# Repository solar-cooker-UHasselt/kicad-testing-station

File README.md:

# kicad-testing-station

The main board of the [solar cooker](https://github.com/solar-cooker-UHasselt) testing
station: a shield for the
[Arduino UNO R4 WiFi](https://docs.arduino.cc/hardware/uno-r4-wifi/) that logs how a
solar cooker performs. With the firmware
([arduino-code](https://github.com/solar-cooker-UHasselt/arduino-code)) it records:

- the temperature in three pots, with PT100 probes on three MAX31865 circuits
- the solar irradiance, with a pyranometer
- the wind speed, with an anemometer
- the outside temperature, with an AM2315C sensor
- the air pressure and humidity inside the box, with a BME680

Every measurement goes to a CSV file on a microSD card, stamped by a DS3231 real-time
clock, and shows on an LCD. The MAX31865, BME680, DS3231 and microSD circuits are
Adafruit's breakouts, drawn onto the shield as schematic sheets. Each also has its own
repo, see the [board overview](https://solar-cooker-uhasselt.github.io/). The sensors outside the box
connect to screw terminals, the LCD to a 20-pin FPC connector.

- [Board page](https://solar-cooker-uhasselt.github.io/kicad-testing-station/): 3D
  renders, drawings, schematic and board PDF, interactive BOM and the BOM CSV for
  Eurocircuits, rebuilt by CI on every push to `main`
- [Port an Eagle design to KiCad](docs/eagle_to_kicad.md): how the Adafruit and
  Arduino parts were brought into KiCad, and replacing symbols and footprints
- [PCB manufacturing](docs/pcb_manufacturing.md): the Eurocircuits BOM and checking
  part availability
- [KiCad tools](docs/kicad_tools.md): Freerouting, KiBot, KiKit and Kiri

## Installation

### Requirements

- [KiCad 10](https://www.kicad.org/download/), to open and edit the board
- [git](https://git-scm.com), to clone the repo
- Optional, for the checks: [just](https://just.systems)

### Clone

```bash
git clone https://github.com/solar-cooker-UHasselt/kicad-testing-station.git
```

Own symbols, footprints and 3D models are in `external/`, in the repo itself.

## Usage

Open `testing-station.kicad_pro` in KiCad 10. The schematic, with a sheet per breakout
circuit, and the board open from there.

Before committing, run ERC and DRC, reports in `tmp/`:

```bash
just check
```

`just --list` shows the other recipes: PDFs, and the CI workflow run locally.

## Contributing

- Work on a branch and open a pull request to `main`. It merges once CI passes and a code
  owner (listed in [.github/CODEOWNERS](.github/CODEOWNERS)) approves it. `main`
  accepts no force pushes.
- CI runs ERC and DRC on every pull request, through the shared workflows in
  [kicad-ci](https://github.com/solar-cooker-UHasselt/kicad-ci). `just check` runs the
  same check locally. A push to `main` that changes more than Markdown also rebuilds
  the board page.
- Commits follow Conventional Commits, with one change per commit. Types, scopes and the
  ERC/DRC check are in
  [.agents/commit_conventions.md](.agents/commit_conventions.md).
- Changes to the board setup, CI or docs are made and tested in
  [kicad-adafruit-ds3231](https://github.com/solar-cooker-UHasselt/kicad-adafruit-ds3231)
  first, then copied here.

## Authors and acknowledgment

The breakout circuits are Adafruit's designs, by Limor Fried/Ladyada for Adafruit
Industries
([source files](https://learn.adafruit.com/accessing-and-using-adafruit-pcb-design-files/finding-and-downloading)).
The shield follows Arduino's
[UNO R4 WiFi design files](https://docs.arduino.cc/hardware/uno-r4-wifi/). The board
is by Lowie Van Vyve for the UHasselt solar cooker project.

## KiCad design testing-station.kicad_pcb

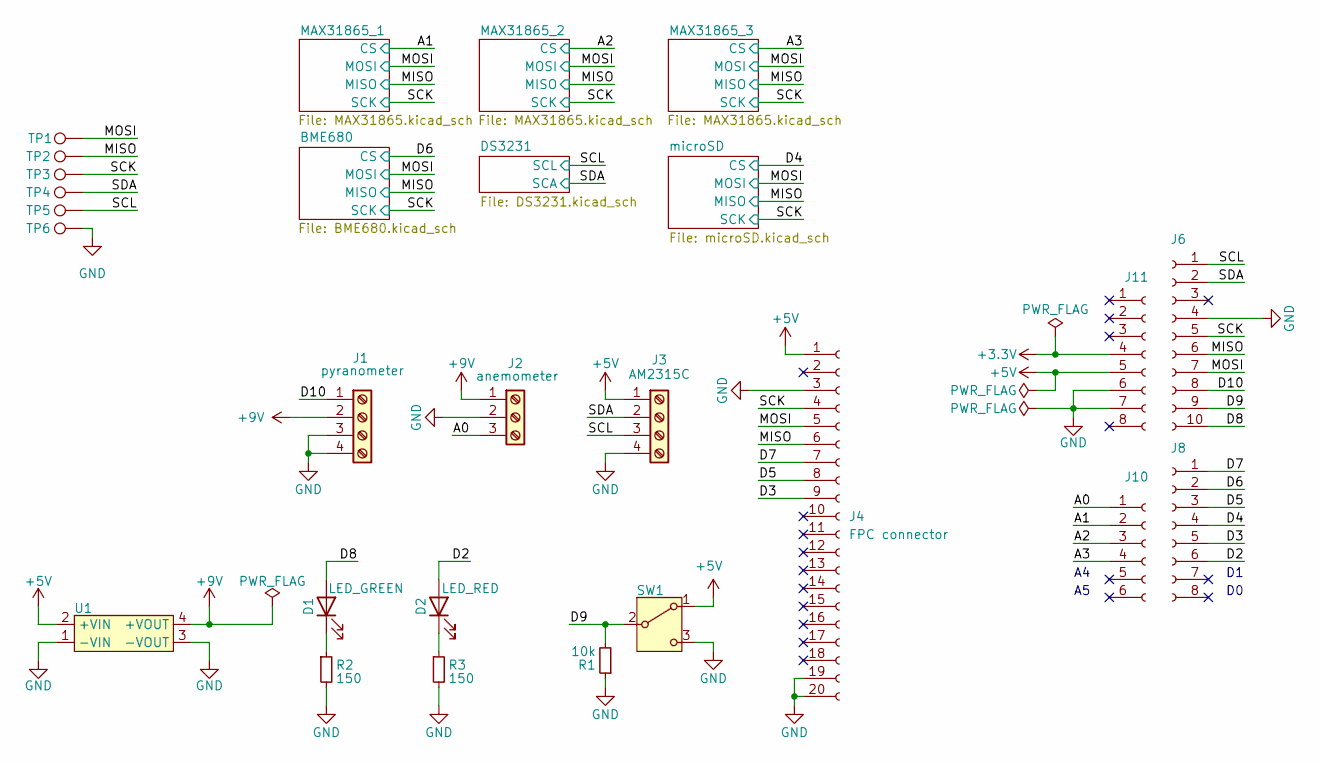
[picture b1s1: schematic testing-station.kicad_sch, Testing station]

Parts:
D1: LED_GREEN; LED_1206_3216Metric_Pad1.42x1.75mm_HandSolder; MPN 150120VS75000
D2: LED_RED; LED_1206_3216Metric_Pad1.42x1.75mm_HandSolder; MPN QTLP650D2TR
J1: pyranometer; TerminalBlock_4Ucon_1x04_P3.50mm_Horizontal; MPN 039357-0004
J2: anemometer; TerminalBlock_4Ucon_1x03_P3.50mm_Horizontal; MPN 039357-0003
J3: AM2315C; TerminalBlock_4Ucon_1x04_P3.50mm_Horizontal; MPN 039357-0004
J4: FPC connector; XF2M-1815-1A; MPN XF2M-1815-1A
J6: Conn_01x10_Socket; PinSocket_1x10_P2.54mm_Vertical; MPN SSQ-110-01-G-S
J8, J11: Conn_01x08_Socket; PinSocket_1x08_P2.54mm_Vertical; MPN SSQ-108-01-G-S
J10: Conn_01x06_Socket; PinSocket_1x06_P2.54mm_Vertical; MPN SSQ-106-01-G-S
R1: 10k; R_1206_3216Metric_Pad1.30x1.75mm_HandSolder; MPN /
R2, R3: 150; R_1206_3216Metric_Pad1.30x1.75mm_HandSolder; MPN /
SW1: 500SSP1S2M2QEA; MPN 500SSP1S2M2QEA
TP1: MOSI; TestPoint_Pad_D1.0mm
TP2: MISO; TestPoint_Pad_D1.0mm
TP3: SCK; TestPoint_Pad_D1.0mm
TP4: SDA; TestPoint_Pad_D1.0mm
TP5: SCL; TestPoint_Pad_D1.0mm
TP6: GND; TestPoint_Pad_D1.0mm
U1: TBA_1-0519; MPN TBA 1-0519

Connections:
+3.3V: J11.4; also elsewhere on the board
+5V: J3.1, J4.1, J11.5, SW1.1 (A), U1.2 (+VIN); also elsewhere on the board
+9V: J1.2, J2.1, U1.4 (+VOUT)
/A0: J2.3, J10.1
/A1: J10.2; also elsewhere on the board
/A2: J10.3; also elsewhere on the board
/A3: J10.4; also elsewhere on the board
/D2: D2.2 (A), J8.6
/D3: J4.9, J8.5
/D4: J8.4; also elsewhere on the board
/D5: J4.8, J8.3
/D6: J8.2; also elsewhere on the board
/D7: J4.7, J8.1
/D8: D1.2 (A), J6.10
/D9: J6.9, R1.2, SW1.2 (B)
/D10: J1.1, J6.8
/MISO: J4.6, J6.6, TP2.1; also elsewhere on the board
/MOSI: J4.5, J6.7, TP1.1; also elsewhere on the board
/SCK: J4.4, J6.5, TP3.1; also elsewhere on the board
/SCL: J3.3, J6.1, TP5.1; also elsewhere on the board
/SDA: J3.2, J6.2, TP4.1; also elsewhere on the board
GND: J1.3, J1.4, J2.2, J3.4, J4.3, J4.19, J4.20, J6.4, J11.6, J11.7, R1.1, R2.2, R3.2, SW1.3 (C), TP6.1, U1.1 (-VIN), U1.3 (-VOUT); also elsewhere on the board
unnamed: D1.1 (K), R2.1
unnamed: D2.1 (K), R3.1

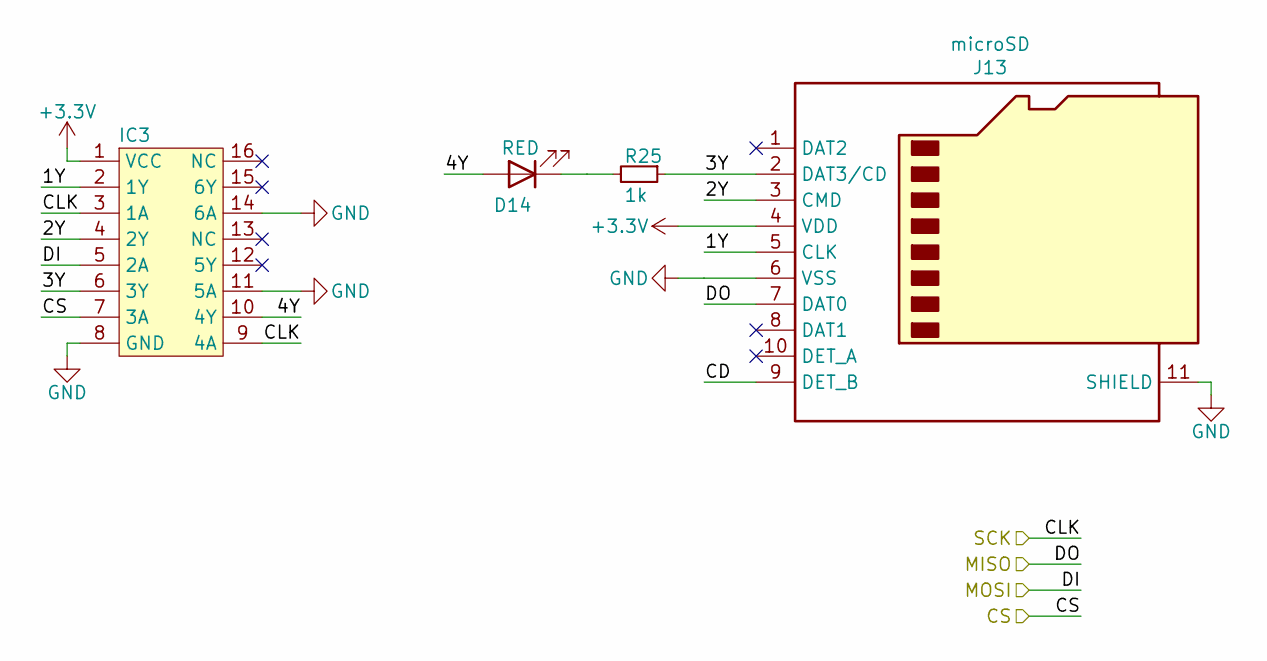
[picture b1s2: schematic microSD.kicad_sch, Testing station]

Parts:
D14: RED; LED_0805_2012Metric; MPN 150080SS75000
IC3: 74HC4050D; SOIC-16_3.9x9.9mm_P1.27mm; MPN 74HC4050D
J13: microSD; MEM2061-01-188-00-A; MPN MEM2061-01-188-00-A
R25: 1k; R_0805_2012Metric; MPN /

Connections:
+3.3V: IC3.1 (VCC), J13.4 (VDD); also elsewhere on the board
/D4: IC3.7 (3A); also elsewhere on the board
/MISO: J13.7 (DAT0); also elsewhere on the board
/MOSI: IC3.5 (2A); also elsewhere on the board
/SCK: IC3.3 (1A), IC3.9 (4A); also elsewhere on the board
/microSD/1Y: IC3.2 (1Y), J13.5 (CLK)
/microSD/2Y: IC3.4 (2Y), J13.3 (CMD)
/microSD/3Y: IC3.6 (3Y), J13.2 (DAT3/CD), R25.1
/microSD/4Y: D14.2 (A), IC3.10 (4Y)
/microSD/CD: J13.9 (DET_B)
GND: IC3.8 (GND), IC3.11 (5A), IC3.14 (6A), J13.6 (VSS), J13.11 (SHIELD); also elsewhere on the board
unnamed: D14.1 (K), R25.2

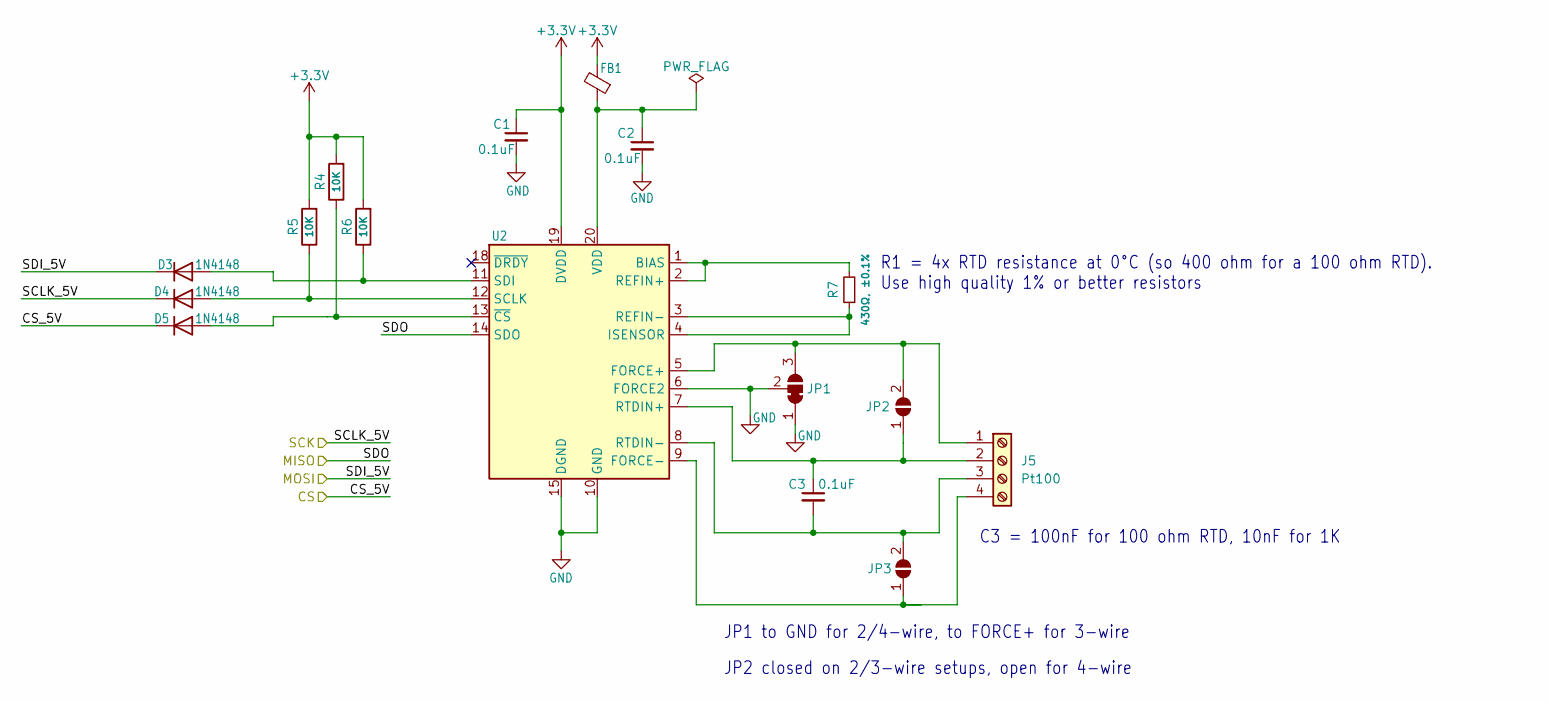
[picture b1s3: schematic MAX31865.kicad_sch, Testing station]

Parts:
C1, C2, C3: 0.1uF; C_0805_2012Metric; MPN /
D3, D4, D5: 1N4148; D_SOD-323; MPN 1N4148WX-TP
FB1: FERRITE-0805NO; LI0805G201R-10; MPN LI0805G201R-10
J5: Pt100; TerminalBlock_4Ucon_1x04_P3.50mm_Horizontal; MPN 039357-0004
JP1: SolderJumper_3_Bridged12; SolderJumper-3_P1.3mm_Bridged12_Pad1.0x1.5mm
JP2, JP3: SOLDERJUMPER; SolderJumper-2_P1.3mm_Open_RoundedPad1.0x1.5mm
R4, R5, R6: 10K; R_0805_2012Metric; MPN /
R7: 430Ω, ±0.1%; R_0805_2012Metric; MPN /
U2: MAX31865; MAX31865ATP+; MPN MAX31865ATP+

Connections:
+3.3V: C1.1, FB1.2, R4.2, R5.2, R6.2, U2.19 (DVDD); also elsewhere on the board
/A1: D5.1 (K); also elsewhere on the board
/MISO: U2.14 (SDO); also elsewhere on the board
/MOSI: D3.1 (K); also elsewhere on the board
/SCK: D4.1 (K); also elsewhere on the board
GND: C1.2, C2.2, JP1.1 (A), JP1.2 (C), U2.6 (FORCE2), U2.10 (GND), U2.15 (DGND), U2.16 (GND), U2.21 (GND); also elsewhere on the board
unnamed: D3.2 (A), R6.1, U2.11 (SDI)
unnamed: D4.2 (A), R5.1, U2.12 (SCLK)
unnamed: D5.2 (A), R4.1, U2.13 (~CS)
unnamed: J5.1, JP1.3 (B), JP2.2 (B), U2.5 (FORCE+)
unnamed: C3.1, J5.2, JP2.1 (A), U2.7 (RTDIN+)
unnamed: C3.2, J5.3, JP3.2 (B), U2.8 (RTDIN-)
unnamed: J5.4, JP3.1 (A), U2.9 (FORCE-)
unnamed: R7.2, U2.1 (BIAS), U2.2 (REFIN+)
unnamed: R7.1, U2.3 (REFIN-), U2.4 (ISENSOR)
unnamed: C2.1, FB1.1, U2.20 (VDD)

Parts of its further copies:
C6, C7, C8, C11, C12, C13: 0.1uF; C_0805_2012Metric; MPN /
D6, D7, D8, D9, D10, D11: 1N4148; D_SOD-323; MPN 1N4148WX-TP
FB2, FB3: FERRITE-0805NO; LI0805G201R-10; MPN LI0805G201R-10
J7, J9: Pt100; TerminalBlock_4Ucon_1x04_P3.50mm_Horizontal; MPN 039357-0004
JP4, JP7: SolderJumper_3_Bridged12; SolderJumper-3_P1.3mm_Bridged12_Pad1.0x1.5mm
JP5, JP6, JP8, JP9: SOLDERJUMPER; SolderJumper-2_P1.3mm_Open_RoundedPad1.0x1.5mm
R8, R9, R10, R12, R13, R14: 10K; R_0805_2012Metric; MPN /
R11, R15: 430Ω, ±0.1%; R_0805_2012Metric; MPN /
U4, U6: MAX31865; MAX31865ATP+; MPN MAX31865ATP+

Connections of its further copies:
+3.3V: C6.1, C11.1, FB2.2, FB3.2, R8.2, R9.2, R10.2, R12.2, R13.2, R14.2, U4.19 (DVDD), U6.19 (DVDD); also elsewhere on the board
/A2: D8.1 (K); also elsewhere on the board
/A3: D11.1 (K); also elsewhere on the board
/MISO: U4.14 (SDO), U6.14 (SDO); also elsewhere on the board
/MOSI: D6.1 (K), D9.1 (K); also elsewhere on the board
/SCK: D7.1 (K), D10.1 (K); also elsewhere on the board
GND: C6.2, C7.2, C11.2, C12.2, JP4.1 (A), JP4.2 (C), JP7.1 (A), JP7.2 (C), U4.6 (FORCE2), U4.10 (GND), U4.15 (DGND), U4.16 (GND), U4.21 (GND), U6.6 (FORCE2), U6.10 (GND), U6.15 (DGND), U6.16 (GND), U6.21 (GND); also elsewhere on the board
unnamed: D6.2 (A), R10.1, U4.11 (SDI)
unnamed: D7.2 (A), R9.1, U4.12 (SCLK)
unnamed: D8.2 (A), R8.1, U4.13 (~CS)
unnamed: D9.2 (A), R14.1, U6.11 (SDI)
unnamed: D10.2 (A), R13.1, U6.12 (SCLK)
unnamed: D11.2 (A), R12.1, U6.13 (~CS)
unnamed: J7.1, JP4.3 (B), JP5.2 (B), U4.5 (FORCE+)
unnamed: C8.1, J7.2, JP5.1 (A), U4.7 (RTDIN+)
unnamed: C8.2, J7.3, JP6.2 (B), U4.8 (RTDIN-)
unnamed: J7.4, JP6.1 (A), U4.9 (FORCE-)
unnamed: J9.1, JP7.3 (B), JP8.2 (B), U6.5 (FORCE+)
unnamed: C13.1, J9.2, JP8.1 (A), U6.7 (RTDIN+)
unnamed: C13.2, J9.3, JP9.2 (B), U6.8 (RTDIN-)
unnamed: J9.4, JP9.1 (A), U6.9 (FORCE-)
unnamed: R11.2, U4.1 (BIAS), U4.2 (REFIN+)
unnamed: R11.1, U4.3 (REFIN-), U4.4 (ISENSOR)
unnamed: C7.1, FB2.1, U4.20 (VDD)
unnamed: R15.2, U6.1 (BIAS), U6.2 (REFIN+)
unnamed: R15.1, U6.3 (REFIN-), U6.4 (ISENSOR)
unnamed: C12.1, FB3.1, U6.20 (VDD)

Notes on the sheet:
JP1 to GND for 2/4-wire, to FORCE+ for 3-wire
C3 = 100nF for 100 ohm RTD, 10nF for 1K
JP2 closed on 2/3-wire setups, open for 4-wire
R1 = 4x RTD resistance at 0°C (so 400 ohm for a 100 ohm RTD). Use high quality 1% or better resistors

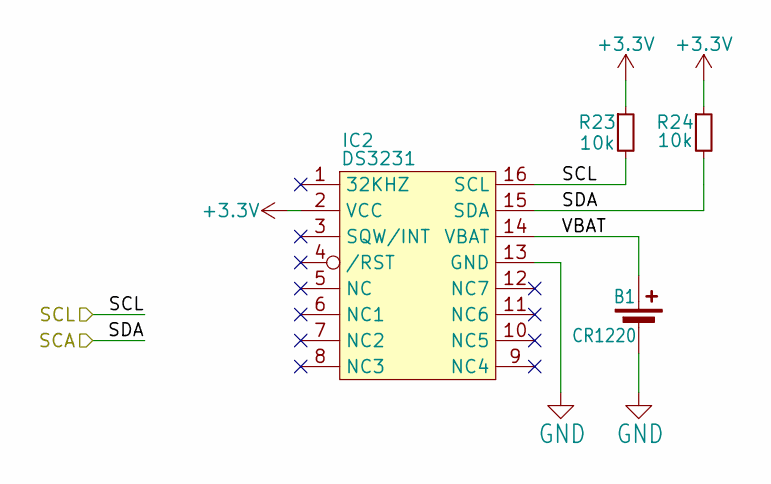
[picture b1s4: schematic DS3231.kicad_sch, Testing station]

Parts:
B1: CR1220; MPN 3001
IC2: DS3231; SOIC-16W_7.5x10.3mm_P1.27mm; MPN DS3231M+TRL
R23, R24: 10k; R_0805_2012Metric; MPN /

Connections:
+3.3V: IC2.2 (VCC), R23.1, R24.1; also elsewhere on the board
/DS3231/VBAT: B1.1 (+), IC2.14 (VBAT)
/SCL: IC2.16 (SCL), R23.2; also elsewhere on the board
/SDA: IC2.15 (SDA), R24.2; also elsewhere on the board
GND: B1.2 (-), IC2.13 (GND); also elsewhere on the board

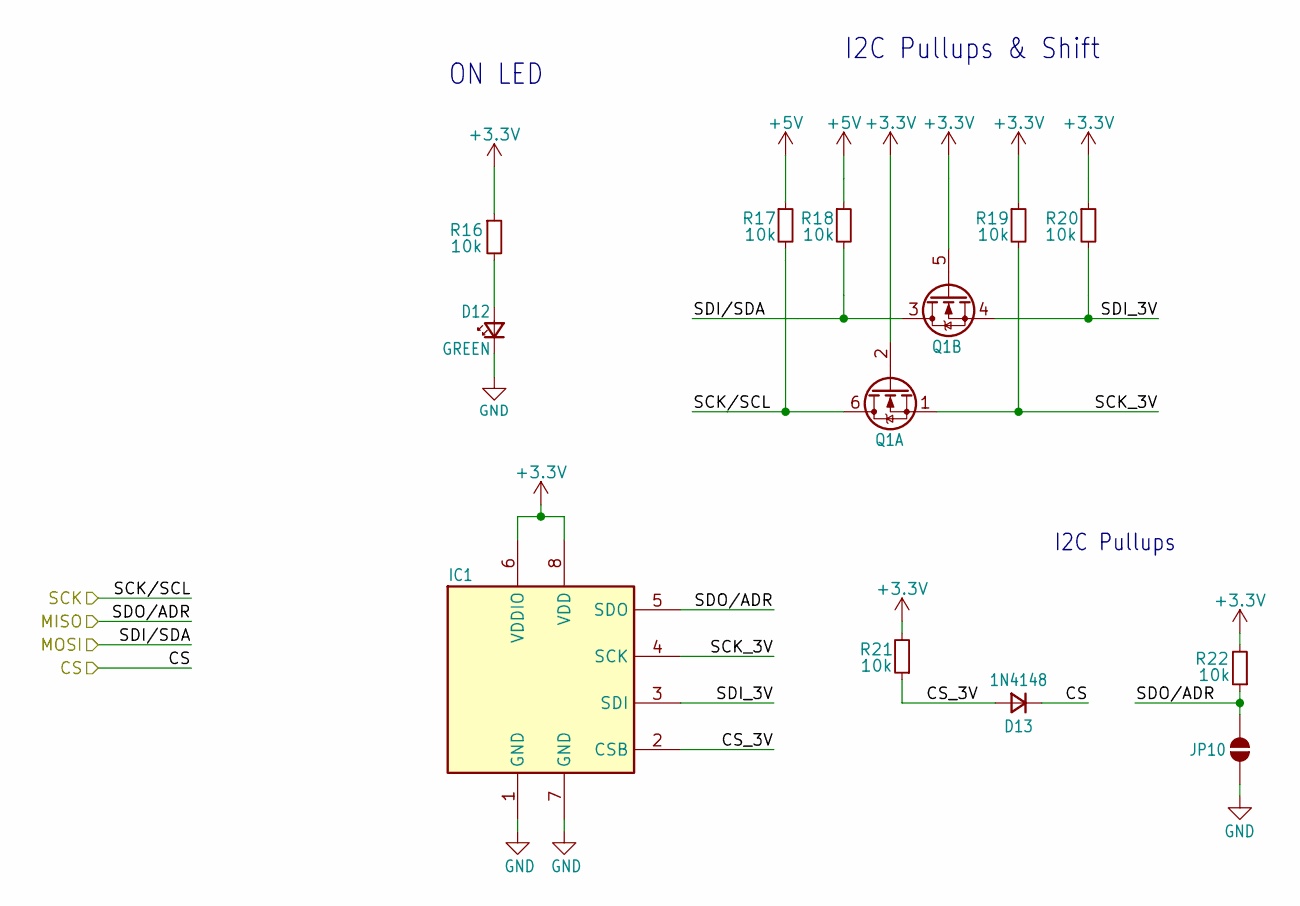
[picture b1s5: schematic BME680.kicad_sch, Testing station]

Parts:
D12: GREEN; LED_0603_1608Metric; MPN 150060GS75000
D13: 1N4148; D_SOD-323; MPN 1N4148WX-TP
IC1: BME680; Bosch_LGA-8_3x3mm_P0.8mm_ClockwisePinNumbering; MPN BME680
JP10: SOLDERJUMPER; SolderJumper-2_P1.3mm_Open_TrianglePad1.0x1.5mm
Q1: BSS138; SOT-363_SC-70-6; MPN BSS138DWQ-7
R16, R17, R18, R19, R20, R21, R22: 10k; R_0603_1608Metric; MPN /

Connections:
+3.3V: IC1.6 (VDDIO), IC1.8 (VDD), Q1.2 (G), Q1.5 (G), R16.1, R19.1, R20.1, R21.2, R22.2; also elsewhere on the board
+5V: R17.1, R18.1; also elsewhere on the board
/BME680/CS_3V: D13.2 (A), IC1.2 (CSB), R21.1
/BME680/SCK_3V: IC1.4 (SCK), Q1.1 (S), R19.2
/BME680/SDI_3V: IC1.3 (SDI), Q1.4 (S), R20.2
/D6: D13.1 (K); also elsewhere on the board
/MISO: IC1.5 (SDO), JP10.1 (A), R22.1; also elsewhere on the board
/MOSI: Q1.3 (D), R18.2; also elsewhere on the board
/SCK: Q1.6 (D), R17.2; also elsewhere on the board
GND: D12.1 (K), IC1.1 (GND), IC1.7 (GND), JP10.2 (B); also elsewhere on the board
unnamed: D12.2 (A), R16.2

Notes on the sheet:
I2C Pullups
I2C Pullups & Shift
ON LED

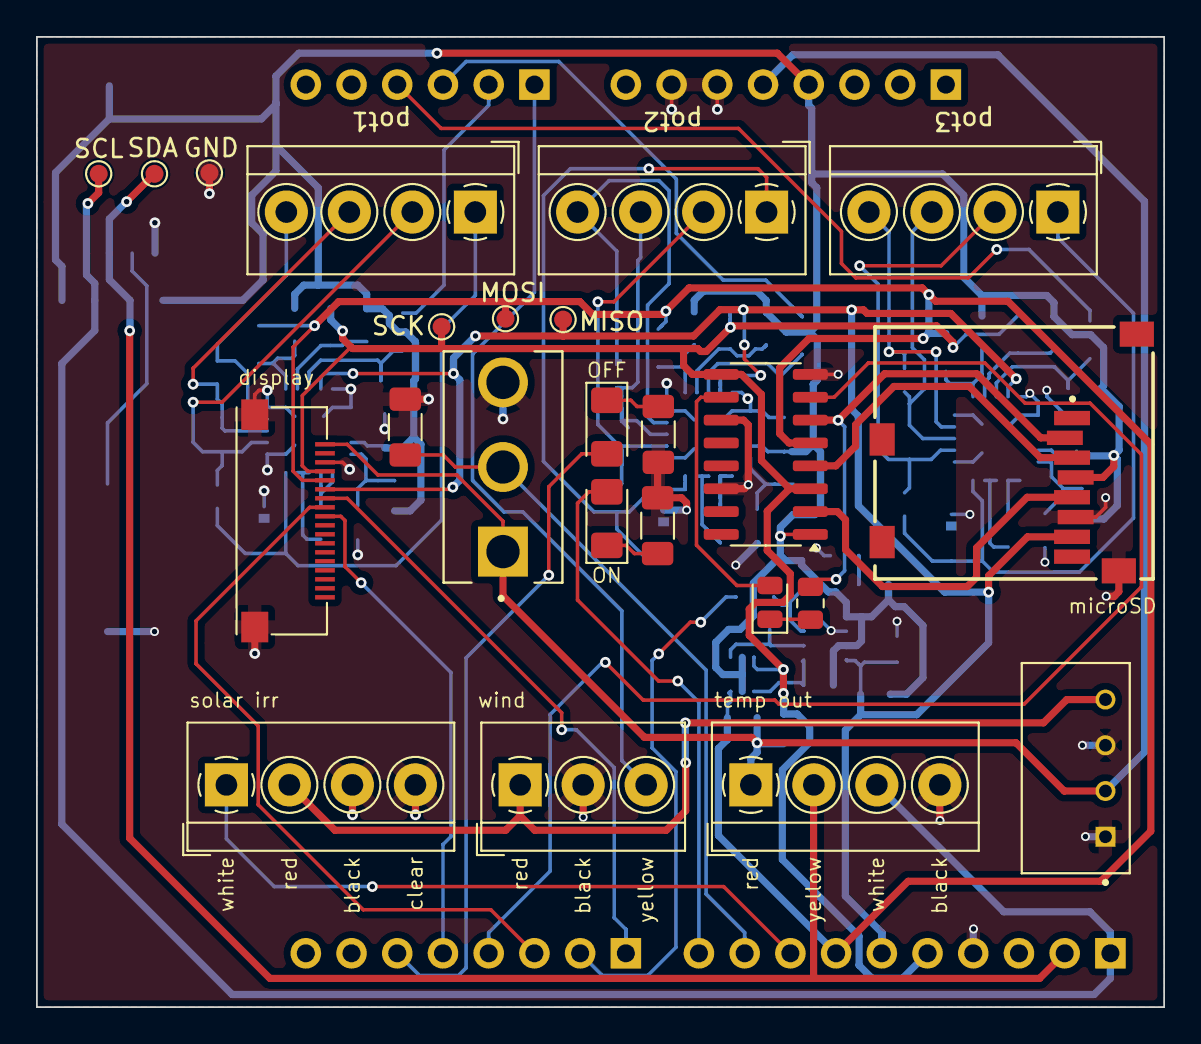
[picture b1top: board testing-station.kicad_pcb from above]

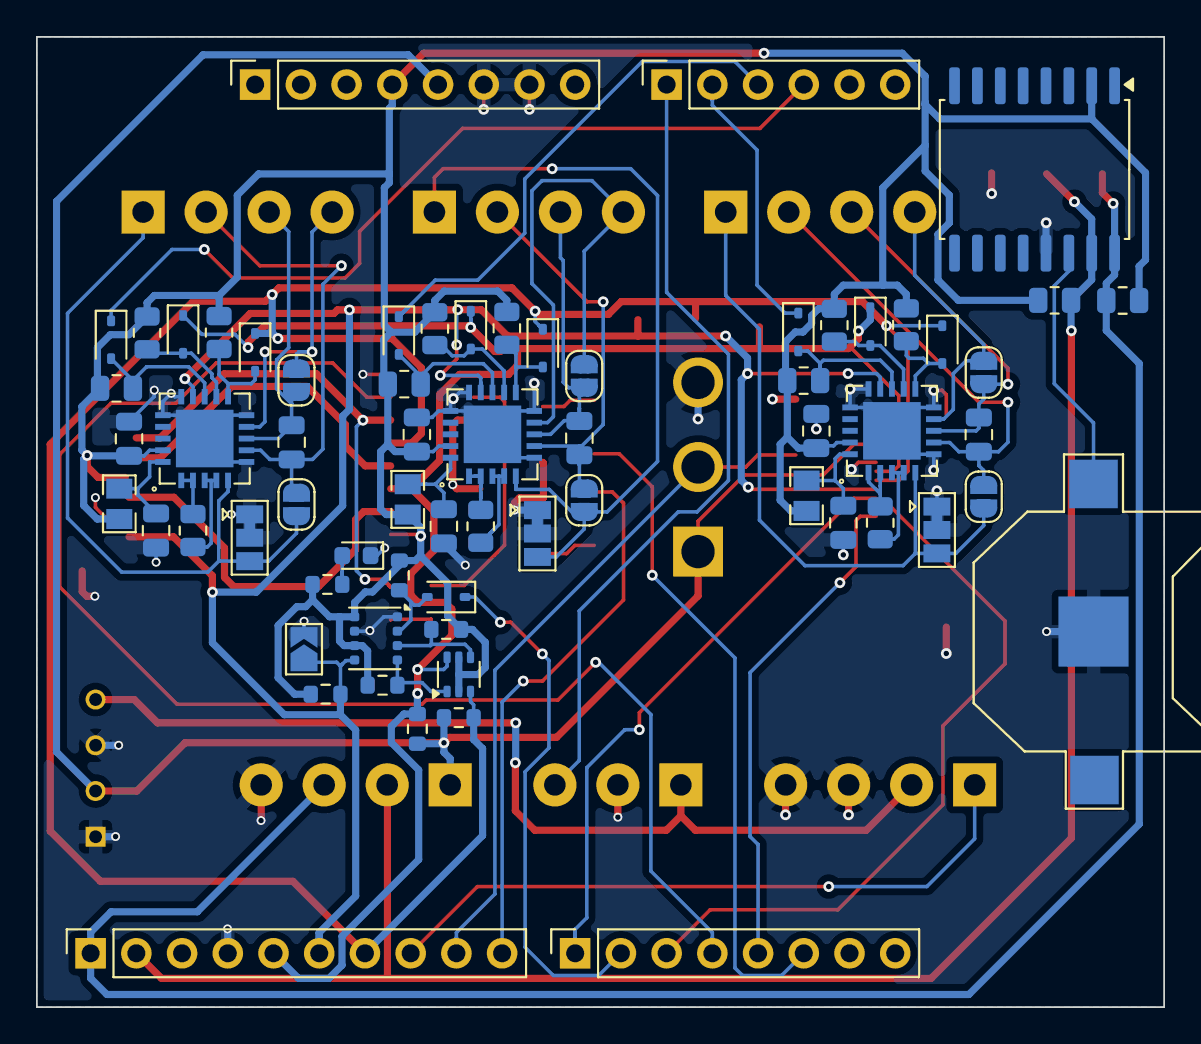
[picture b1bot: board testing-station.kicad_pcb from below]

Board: 4 copper layers, 62.6 x 53.9 mm, 89 parts (65 on the bottom side), 64 nets.

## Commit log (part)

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2024-03-07 .gitignore update
2024-03-07 blank KiCad project
2024-03-07 added drawing sheet
2024-04-03 changed copper finish + solder mask and silkscreen color update
2024-04-04 KiBot DRC check workflow
2024-04-05 switched to 4 layer board
2024-05-17 added MAX31865 schematic page
2024-05-17 added BME680 schematic page
2024-05-17 added DS3231 schematic page
2024-05-18 added 2 more MAX31865
2024-05-18 added microSD schematic page
2024-05-18 added Arduino UNO R4 in root sheet
2024-05-18 added pyrano, anemo, AM2315C, power supply, LEDs, switch and FPC connector in schematic
2024-05-18 removed connectors from modules
2024-05-18 added MAX31865 external files
2024-05-18 restructuring of external files
2024-05-18 added DS3231 external files
2024-05-18 added microSD external files
2024-05-18 added missing external files for PSU and switch + footprints update
2024-05-18 added PCB layout
2024-05-18 removed mouting holes
2024-05-18 changed to 2 layer board + created ground and +5V planes
2024-05-18 removed voltage regulators of each individual module
2024-05-18 MAX31865 routed on PCB
2024-05-18 DS3231 routed on PCB
2024-05-18 BME680 routed on PCB
2024-05-18 changed Arduino symbol to connectors only
2024-05-18 finished routing
2024-05-18 autorouting
2024-05-18 more compact format
2024-05-18 drc fix
2024-05-18 workflow update
2024-05-18 BOM update
2024-05-19 small layout change PCB
2024-05-19 silkscreen update
2024-05-21 implemented Eurocircuits design remarks
2024-05-23 final on/off LED update
2024-06-10 BOM presets update
2024-08-23 compacter PCB design + debugging improvements pyranometer pin change, AM2315C I2C wiring fix, changed stackup, added ground vias, double sided PCB
